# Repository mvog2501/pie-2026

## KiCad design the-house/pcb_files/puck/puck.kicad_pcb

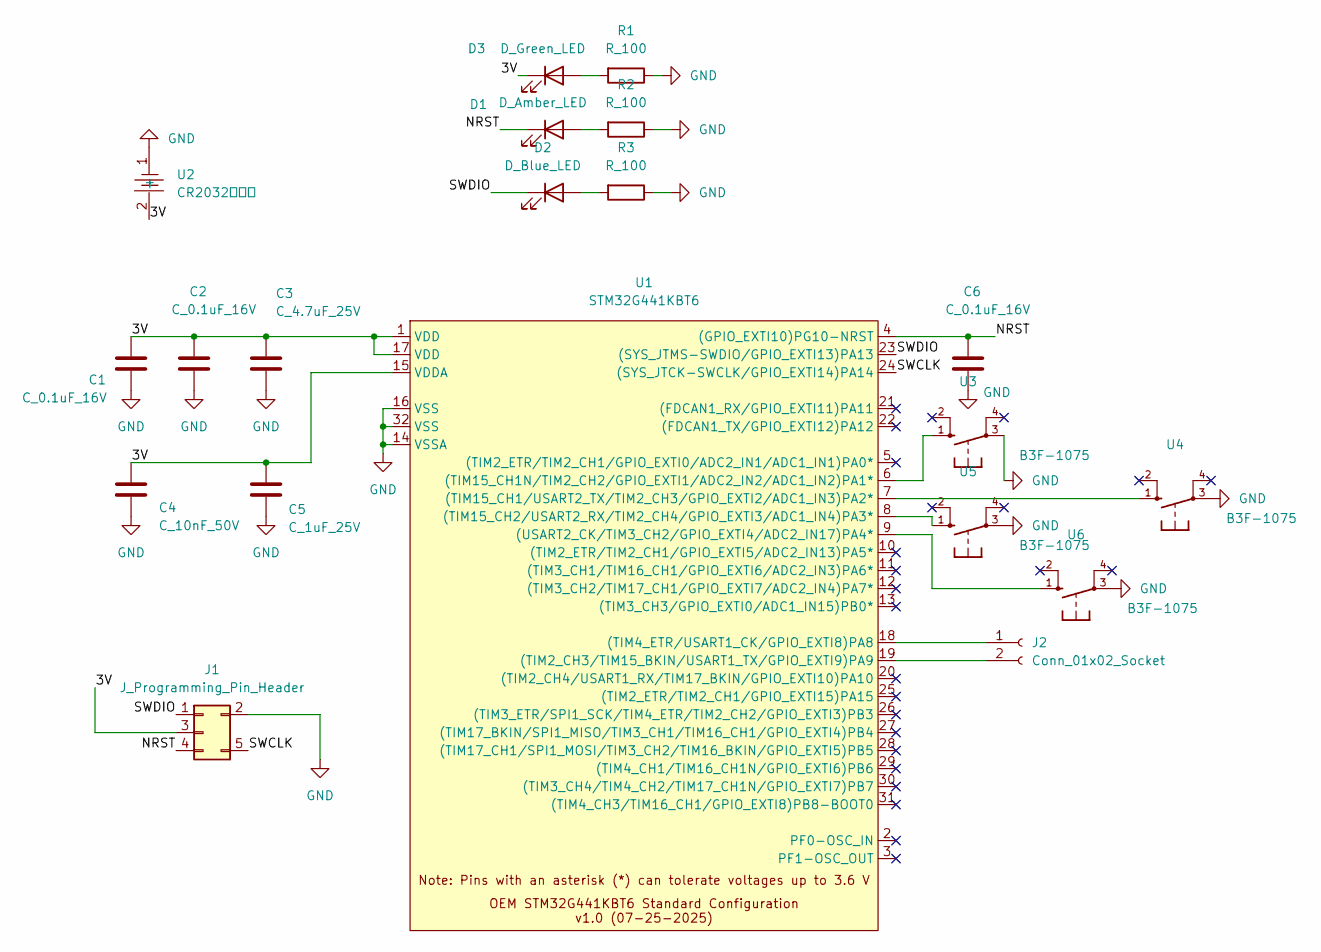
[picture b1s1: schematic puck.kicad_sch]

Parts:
C1, C2, C6: C_0.1uF_16V; C_0603_1608Metric; MPN C0603C104Z4VACTU
C3: C_4.7uF_25V; C_0603_1608Metric; MPN GRT188R61E475ME13D
C4: C_10nF_50V; C_0603_1608Metric; MPN CL10B103KB8NNNC
C5: C_1uF_25V; C_0603_1608Metric; MPN CL10B105KA8NNNC
D1: D_Amber_LED; D_0805_2012Metric; MPN LTST-C171AKT
D2: D_Blue_LED; D_0805_2012Metric; MPN LTST-C171TBKT
D3: D_Green_LED; D_0805_2012Metric; MPN LTST-C170KGKT
J1: J_Programming_Pin_Header; J_Programming_Pin_Header_Keyed
J2: Conn_01x02_Socket; PinSocket_1x02_P1.00mm_Vertical
R1, R2, R3: R_100; R_0603_1608Metric; MPN RMCF0603FT100R
U1: STM32G441KBT6; LQFP-32_7x7mm_P0.8mm
U2: CR2032电池座; BAT-SMD_CR2032_C9900016310; MPN CR2032电池座; LCSC Part C9900016310
U3, U4, U5, U6: B3F-1075

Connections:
/3V: C1.1, C2.1, C3.1, C4.1, C5.1, D3.1 (K), J1.3, U1.1 (VDD), U1.15 (VDDA), U1.17 (VDD), U2.2 (+)
/NRST: C6.1, D1.1 (K), J1.4, U1.4 ((GPIO_EXTI10)PG10-NRST)
/SWCLK: J1.5, U1.24 ((SYS_JTCK-SWCLK/GPIO_EXTI14)PA14)
/SWDIO: D2.1 (K), J1.1, U1.23 ((SYS_JTMS-SWDIO/GPIO_EXTI13)PA13)
GND: C1.2, C2.2, C3.2, C4.2, C5.2, C6.2, J1.2, R1.1, R2.1, R3.1, U1.14 (VSSA), U1.16 (VSS), U1.32 (VSS), U2.1 (-), U3.3, U4.3, U5.3, U6.3
unnamed: D1.2 (A), R2.2
unnamed: D2.2 (A), R3.2
unnamed: D3.2 (A), R1.2
unnamed: J2.1, U1.18 ((TIM4_ETR/USART1_CK/GPIO_EXTI8)PA8)
unnamed: J2.2, U1.19 ((TIM2_CH3/TIM15_BKIN/USART1_TX/GPIO_EXT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)
unnamed: U1.6 ((TIM15_CH1N/TIM2_CH2/GPIO_EXTI1/ADC2_IN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), U3.1
unnamed: U1.7 ((TIM15_CH1/USART2_TX/TIM2_CH3/GPIO_EXTI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), U4.1
unnamed: U1.8 ((TIM15_CH2/USART2_RX/TIM2_CH4/GPIO_EXTI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), U5.1
unnamed: U1.9 ((USART2_CK/TIM3_CH2/GPIO_EXTI4/ADC2_IN1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), U6.1

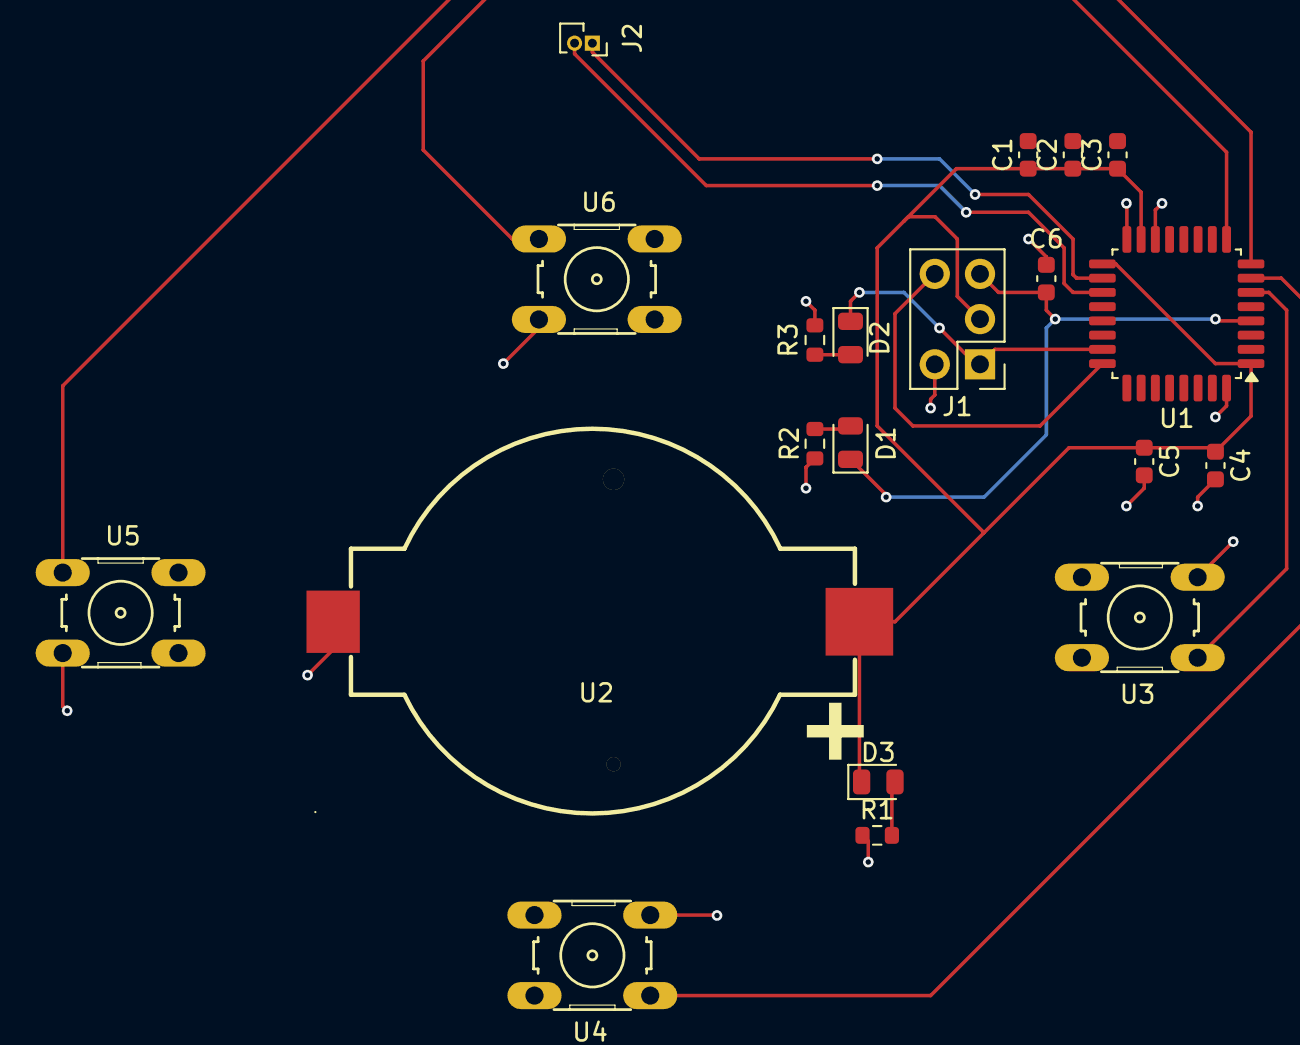
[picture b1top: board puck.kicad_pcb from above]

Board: 2 copper layers, 20 parts (0 on the bottom side), 14 nets.
